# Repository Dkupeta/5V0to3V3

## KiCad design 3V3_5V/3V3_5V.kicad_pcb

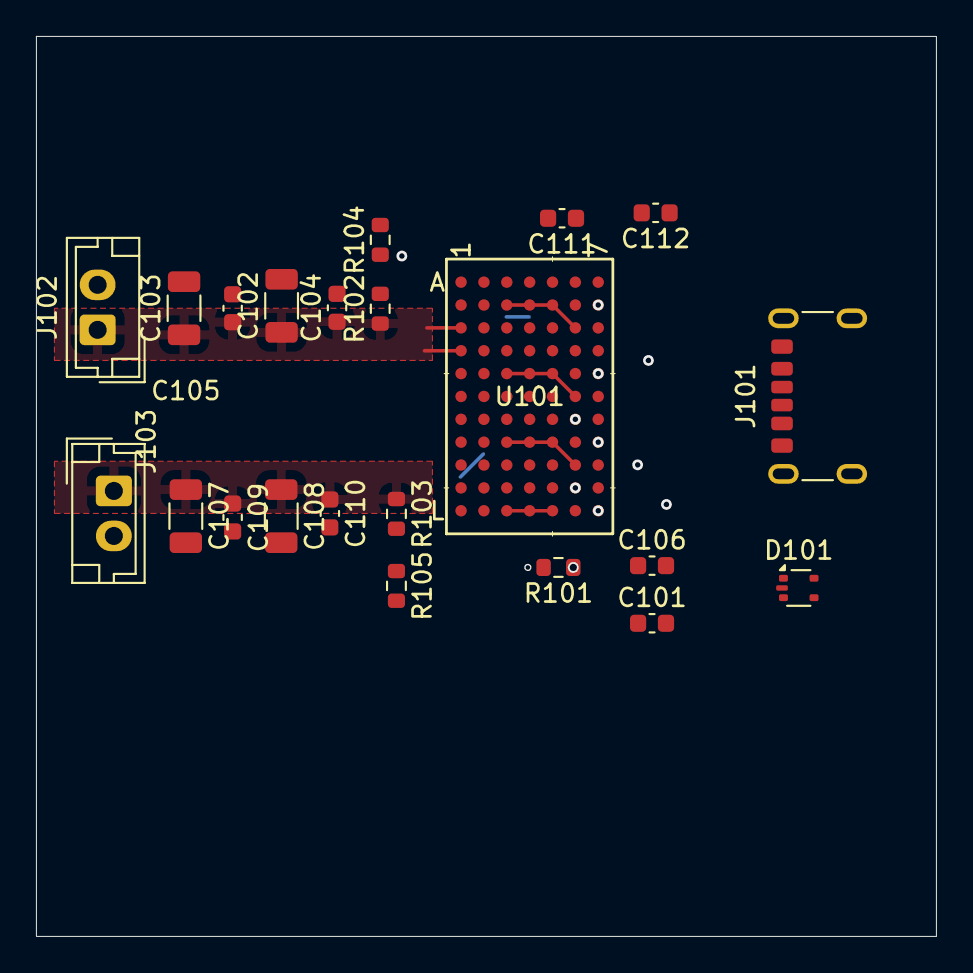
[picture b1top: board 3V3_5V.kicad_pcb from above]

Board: 2 copper layers, 50.0 x 50.0 mm, 22 parts (0 on the bottom side), 14 nets.

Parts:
C101, C106: 1nF; C_0603_1608Metric
C102, C103, C107, C108: 47uF; C_1206_3216Metric
C104, C105, C109, C110: 22uF; C_0603_1608Metric
C111, C112: 1n; C_0603_1608Metric
D101: PESD5V0L4UW; SOT-665
J101: USB_C_Receptacle_PowerOnly_6P; USB_C_Receptacle_GCT_USB4125-xx-x-0190_6P_TopMnt_Horizontal
J102, J103: Conn_01x02_Pin; JST_EH_B2B-EH-A_1x02_P2.50mm_Vertical
R101: 0; R_0603_1608Metric
R102, R103: 60.4k; R_0603_1608Metric
R104, R105: 13.3k; R_0603_1608Metric
U101: LTM4644EY-1-PBF; LGA77_9X15_ADI

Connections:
+3.3VA: C102.1, C103.1, C104.1, C105.1, J102.1, R102.1, U101.A1 (VOUT1), U101.A2 (VOUT1), U101.A3 (VOUT1), U101.C1 (VOUT2), U101.D1 (VOUT2), U101.D2 (VOUT2)
+3.3VB: C107.1, C108.1, C109.1, C110.1, J103.1, R103.1, U101.F1 (VOUT3), U101.G1 (VOUT3), U101.G2 (VOUT3), U101.J1 (VOUT4), U101.J5 (VOUT4), U101.K1 (VOUT4), U101.K2 (VOUT4)
/COMP: U101.B7 (COMP1), U101.E7 (COMP2), U101.H7 (COMP3), U101.L7 (COMP4)
/FB1: R102.2, R104.1, U101.A7 (FB1), U101.D7 (FB2)
/FB2: R103.2, R105.1, U101.G7 (FB3), U101.J7 (FB4)
/INTVcc1: U101.C4 (INTVCC1), U101.F4 (INTVCC2)
/INTVcc2: U101.J4 (INTVCC3), U101.K5 (INTVCC4)
/PG1: U101.C2 (PGOOD2), U101.C3 (PGOOD1)
/PG2: U101.F2 (PGOOD3), U101.J2 (PGOOD4)
/SGND: R101.1, U101.B6 (MODE1), U101.E6 (MODE2), U101.F7 (SGND), U101.H6 (MODE3), U101.L6 (MODE4)
/TR1/SS1: C111.1, C112.1, U101.A6 (TRACK/SS1), U101.D6 (TRACK/SS2)
/TR2/SS2: C101.2, C106.2, U101.G6 (TRACK/SS3), U101.K6 (TRACK/SS4)
/Vin: D101.1 (K1), J101.A9 (VBUS), J101.B9 (VBUS), U101.B3 (VIN1), U101.B4 (VIN1), U101.B5 (SVIN1), U101.C6 (RUN1), U101.E3 (VIN2), U101.E4 (VIN2), U101.E5 (SVIN2), U101.F6 (RUN2), U101.H3 (VIN3), U101.H4 (VIN3), U101.H5 (SVIN3), U101.J6 (RUN3), U101.K7 (RUN4), U101.L3 (VIN4), U101.L4 (VIN4), U101.L5 (SVIN4)
GND: C101.1, C102.2, C103.2, C104.2, C105.2, C106.1, C107.2, C108.2, C109.2, C110.2, C111.2, C112.2, D101.2 (A), J101.A5 (CC1), J101.A12 (GND), J101.B5 (CC2), J101.B12 (GND), J102.2, J103.2, R101.2, R104.2, R105.2, U101.A4 (GND), U101.A5 (GND), U101.B1 (GND), U101.B2 (GND), U101.C5 (GND), U101.D3 (GND), U101.D4 (GND), U101.D5 (GND), U101.E1 (GND), U101.E2 (GND), U101.F5 (GND), U101.G3 (GND), U101.G4 (GND), U101.G5 (GND), U101.H1 (GND), U101.H2 (GND), U101.K3 (GND), U101.K4 (GND), U101.L1 (GND), U101.L2 (GND)

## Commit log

2024-11-30 5V to 3V3 buck
    simulation file from tlspice
2024-11-30 edit schematic and PCB layout
2024-12-29 add to sch and pcb
